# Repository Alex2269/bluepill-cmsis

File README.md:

```    
bluepill-cmsis:
examples SPL (Standard Peripheral Library).

StdPeriph_Lib=${HOME}/stm32lib/
mkdir  -p "${StdPeriph_Lib}"

sfm32f1 Libraries
unzip  zip-stm32f1_stdperiph_lib/stm32f1_stdperiph_lib.zip -d "${StdPeriph_Lib}"

rm stm32f1_stdperiph_lib.zip

depends: make cmake gcc g++ gcc-arm-none-eabi gdb-arm-none-eabi libusb-dev
apt install make cmake gcc g++ gcc-arm-none-eabi gdb-arm-none-eabi libusb-dev

port code from http://www.avislab.com/
```

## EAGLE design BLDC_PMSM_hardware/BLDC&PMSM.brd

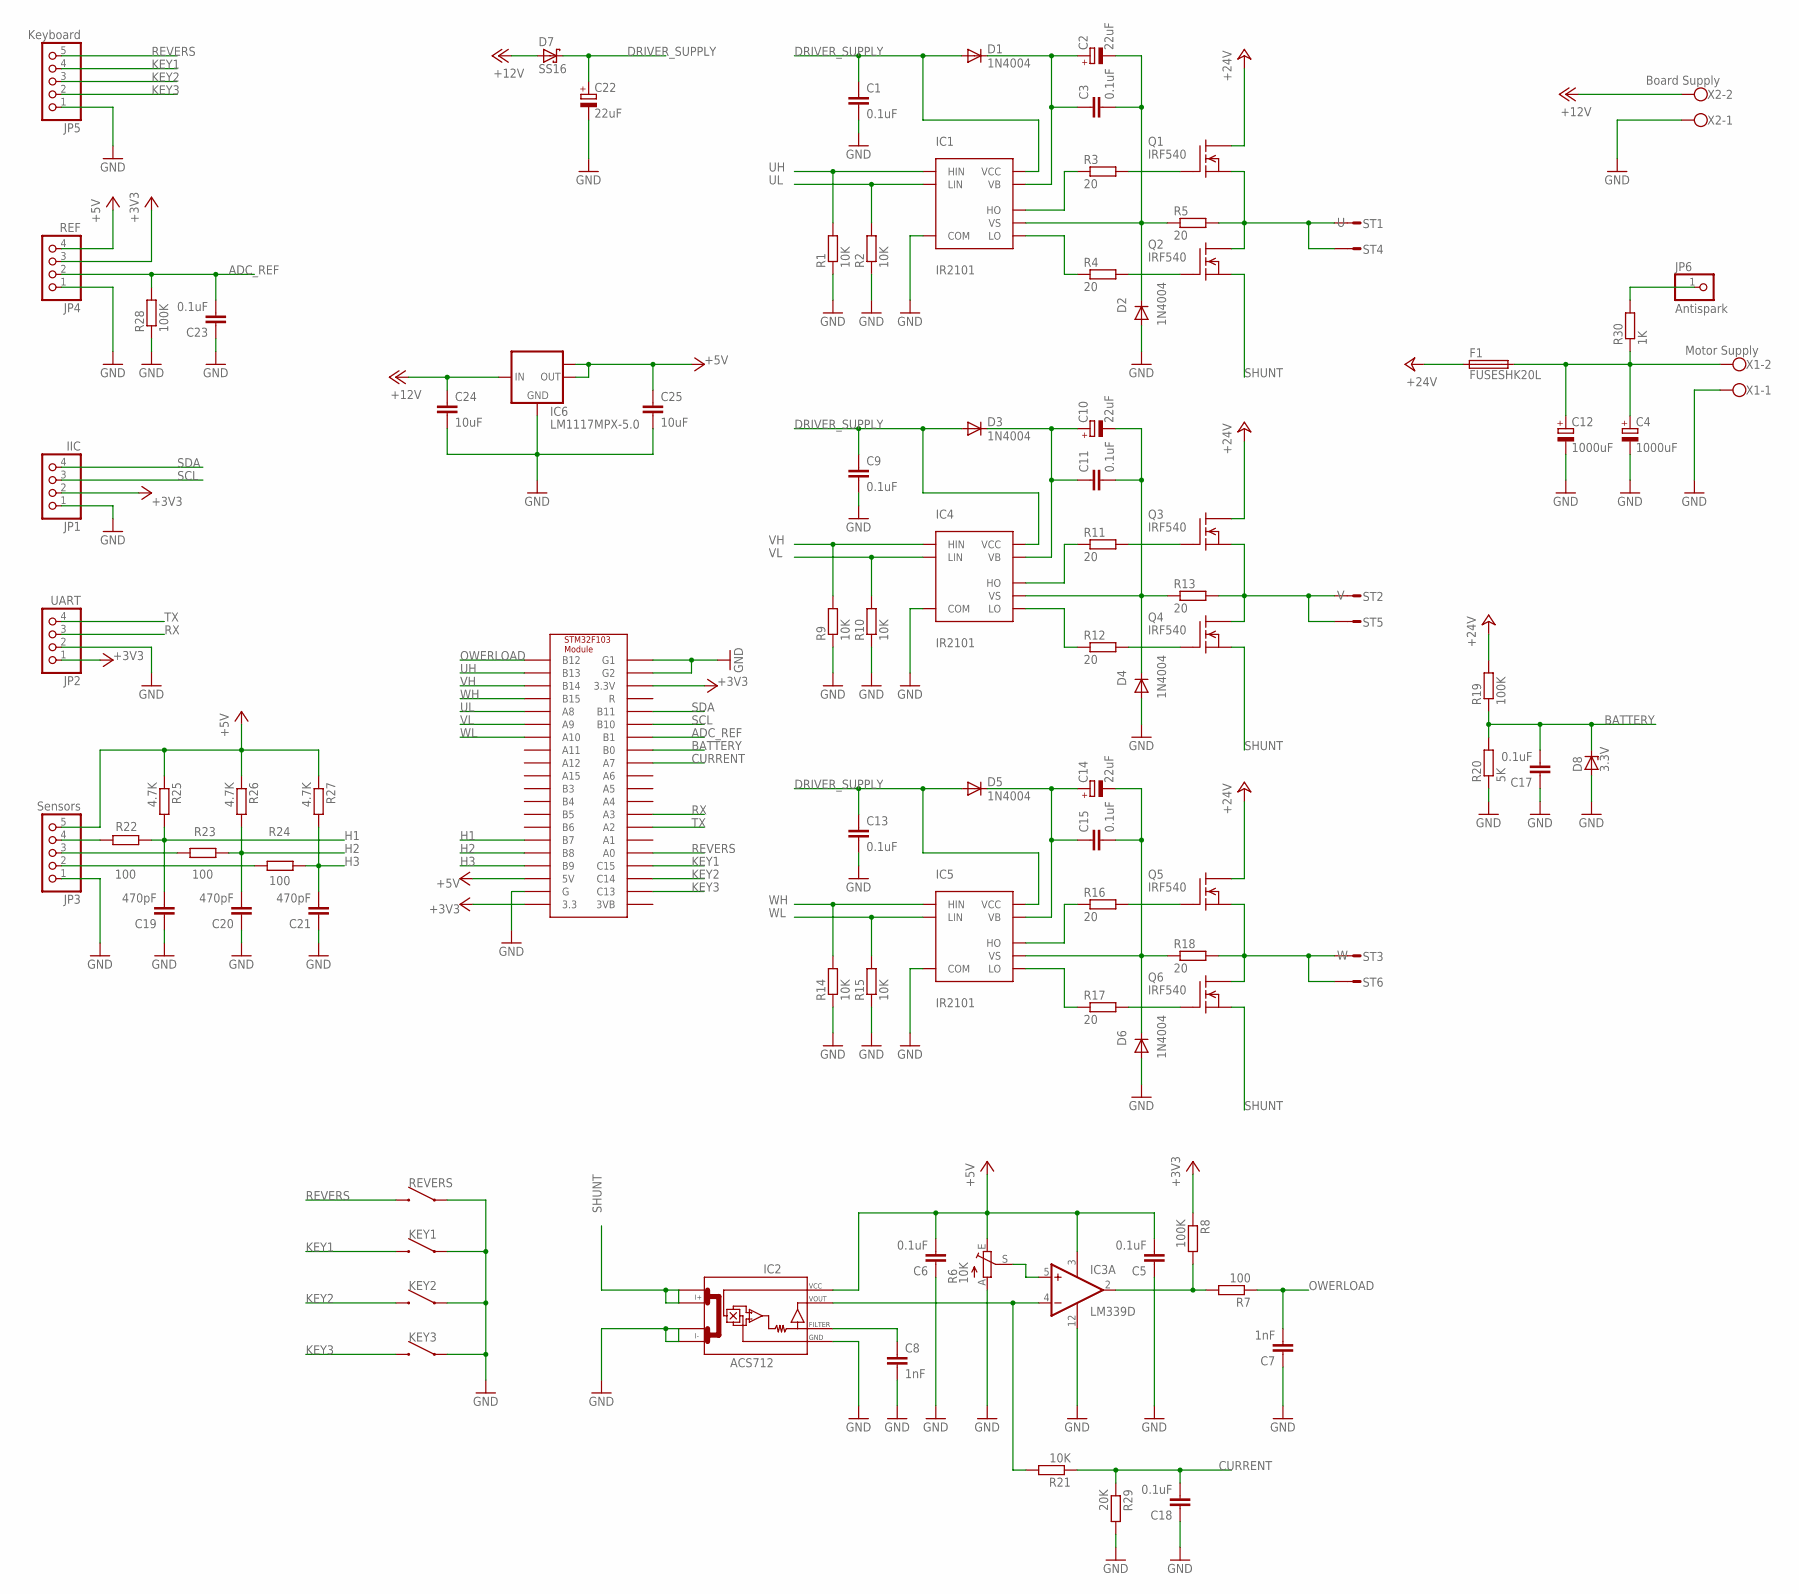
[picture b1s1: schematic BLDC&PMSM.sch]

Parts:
C1, C3, C5, C6, C9, C11, C13, C15, C17, C18, C23: 0.1uF; C0805K
C2, C10, C14, C22: 22uF; E2-5
C4, C12: 1000uF; E5-13
C7, C8: 1nF; C0805K
C19, C20, C21: 470pF; C0805K
C24: 10uF; C0805K
C25: 10uF; C1206K
D1, D2, D3, D4, D5, D6: 1N4004; DO41-10
D7: SS16; SMB
D8: 3.3V; SMB
F1: FUSESHK20L; SHK20L
IC1, IC4, IC5: IR2101; SO08
IC2: ACS712; SO08
IC3: LM339D; SO14
IC6: LM1117MPX-5.0; SOT223
JP1: IIC; 1X04
JP2: UART; 1X04
JP3: Sensors; 1X05
JP4: REF; 1X04
JP5: Keyboard; 1X05
JP6: Antispark; 1X01
KEY1, KEY2, KEY3: SWITCH
Q1, Q2, Q3, Q4, Q5, Q6: IRF540; TO220
R1, R2, R9, R10, R14, R15, R21: 10K; M0805
R3, R4, R5, R11, R12, R13, R16, R17, R18: 20; M0805
R6: 10K; CA6V
R7, R22, R23, R24: 100; M0805
R8, R19, R28: 100K; M0805
R20: 5K; M0805
R25, R26, R27: 4.7K; M0805
R29: 20K; M0805
R30: 1K; M0805
REVERS: SWITCH
ST1, ST2, ST3, ST4, ST5, ST6: ST2,8
U$1: STM32F103MODULE
X1: Motor Supply; W237-102
X2: Board Supply; W237-102

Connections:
3VB: U$1.P$40 (3VB)
+3V3: JP1.2, JP2.1, JP4.3, R8.1, U$1.P$20 (3.3), U$1.P$23 (3.3V)
+5V: C5.2, C6.2, C25.1, IC2.8 (VCC), IC3.3 (V+), IC6.2 (OUT), IC6.TAB (OUT1), JP3.5, JP4.4, R6.E, R25.1, R26.1, R27.1, U$1.P$18 (5V)
+12V: C24.1, D7.A, IC6.3 (IN), X2.2
+24V: F1.1A (1), Q1.2 (D), Q3.2 (D), Q5.2 (D), R19.2
ADC_REF: C23.2, JP4.2, R28.2, U$1.P$27 (B1)
BATTERY: C17.2, D8.C, R19.1, R20.2, U$1.P$28 (B0)
CURRENT: C18.2, R21.1, R29.1, U$1.P$29 (A7)
DRIVER_SUPPLY: C1.1, C9.1, C13.1, C22.+, D1.A, D3.A, D5.A, D7.C, IC1.1 (VCC), IC4.1 (VCC), IC5.1 (VCC)
GND: C1.2, C4.-, C5.1, C6.1, C7.1, C8.2, C9.2, C12.-, C13.2, C17.1, C18.1, C19.1, C20.1, C21.1, C22.-, C23.1, C24.2, C25.2, D2.A, D4.A, D6.A, D8.A, IC1.4 (COM), IC2.3 (I-_0), IC2.4 (I-_1), IC2.5 (GND), IC3.12 (GND), IC4.4 (COM), IC5.4 (COM), IC6.1 (GND), JP1.1, JP2.2, JP3.1, JP4.1, JP5.1, KEY1.P$2 (2), KEY2.P$2 (2), KEY3.P$2 (2), R1.1, R2.1, R6.A, R9.1, R10.1, R14.1, R15.1, R20.1, R28.1, R29.2, REVERS.P$2 (2), U$1.P$19 (G), U$1.P$21 (G1), U$1.P$22 (G2), X1.1, X2.1
H1: C19.2, R22.1, R25.2, U$1.P$15 (B7)
H2: C20.2, R23.1, R26.2, U$1.P$16 (B8)
H3: C21.2, R24.1, R27.2, U$1.P$17 (B9)
KEY1: JP5.4, KEY1.P$1 (1), U$1.P$37 (C15)
KEY2: JP5.3, KEY2.P$1 (1), U$1.P$38 (C14)
KEY3: JP5.2, KEY3.P$1 (1), U$1.P$39 (C13)
unnamed: IC3.5 (+IN), R6.S
unnamed: JP3.4, R22.2
unnamed: IC2.7 (VOUT), IC3.4 (-IN), R21.2
unnamed: IC3.2 (OUT), R7.2, R8.2
unnamed: Q1.1 (G), R3.2
unnamed: Q2.1 (G), R4.2
unnamed: IC1.7 (HO), R3.1
unnamed: IC1.5 (LO), R4.1
unnamed: C2.-, C3.2, D2.C, IC1.6 (VS), R5.1
unnamed: C2.+, C3.1, D1.C, IC1.8 (VB)
unnamed: C8.1, IC2.6 (FILTER)
unnamed: Q3.1 (G), R11.2
unnamed: Q4.1 (G), R12.2
unnamed: IC4.7 (HO), R11.1
unnamed: IC4.5 (LO), R12.1
unnamed: C10.-, C11.2, D4.C, IC4.6 (VS), R13.1
unnamed: C10.+, C11.1, D3.C, IC4.8 (VB)
unnamed: JP3.3, R23.2
unnamed: Q5.1 (G), R16.2
unnamed: Q6.1 (G), R17.2
unnamed: IC5.7 (HO), R16.1
unnamed: IC5.5 (LO), R17.1
unnamed: C14.-, C15.2, D6.C, IC5.6 (VS), R18.1
unnamed: C14.+, C15.1, D5.C, IC5.8 (VB)
unnamed: JP3.2, R24.2
unnamed: C4.+, C12.+, F1.2A (2), R30.1, X1.2
unnamed: JP6.1, R30.2
OWERLOAD: C7.2, R7.1, U$1.P$1 (B12)
REVERS: JP5.5, REVERS.P$1 (1), U$1.P$36 (A0)
RX: JP2.3, U$1.P$33 (A3)
SCL: JP1.3, U$1.P$26 (B10)
SDA: JP1.4, U$1.P$25 (B11)
SHUNT: IC2.1 (I+_0), IC2.2 (I+_1), Q2.3 (S), Q4.3 (S), Q6.3 (S)
TX: JP2.4, U$1.P$34 (A2)
U: Q1.3 (S), Q2.2 (D), R5.2, ST1.1, ST4.1
UH: IC1.2 (HIN), R1.2, U$1.P$2 (B13)
UL: IC1.3 (LIN), R2.2, U$1.P$5 (A8)
V: Q3.3 (S), Q4.2 (D), R13.2, ST2.1, ST5.1
VH: IC4.2 (HIN), R9.2, U$1.P$3 (B14)
VL: IC4.3 (LIN), R10.2, U$1.P$6 (A9)
W: Q5.3 (S), Q6.2 (D), R18.2, ST3.1, ST6.1
WH: IC5.2 (HIN), R14.2, U$1.P$4 (B15)
WL: IC5.3 (LIN), R15.2, U$1.P$7 (A10)

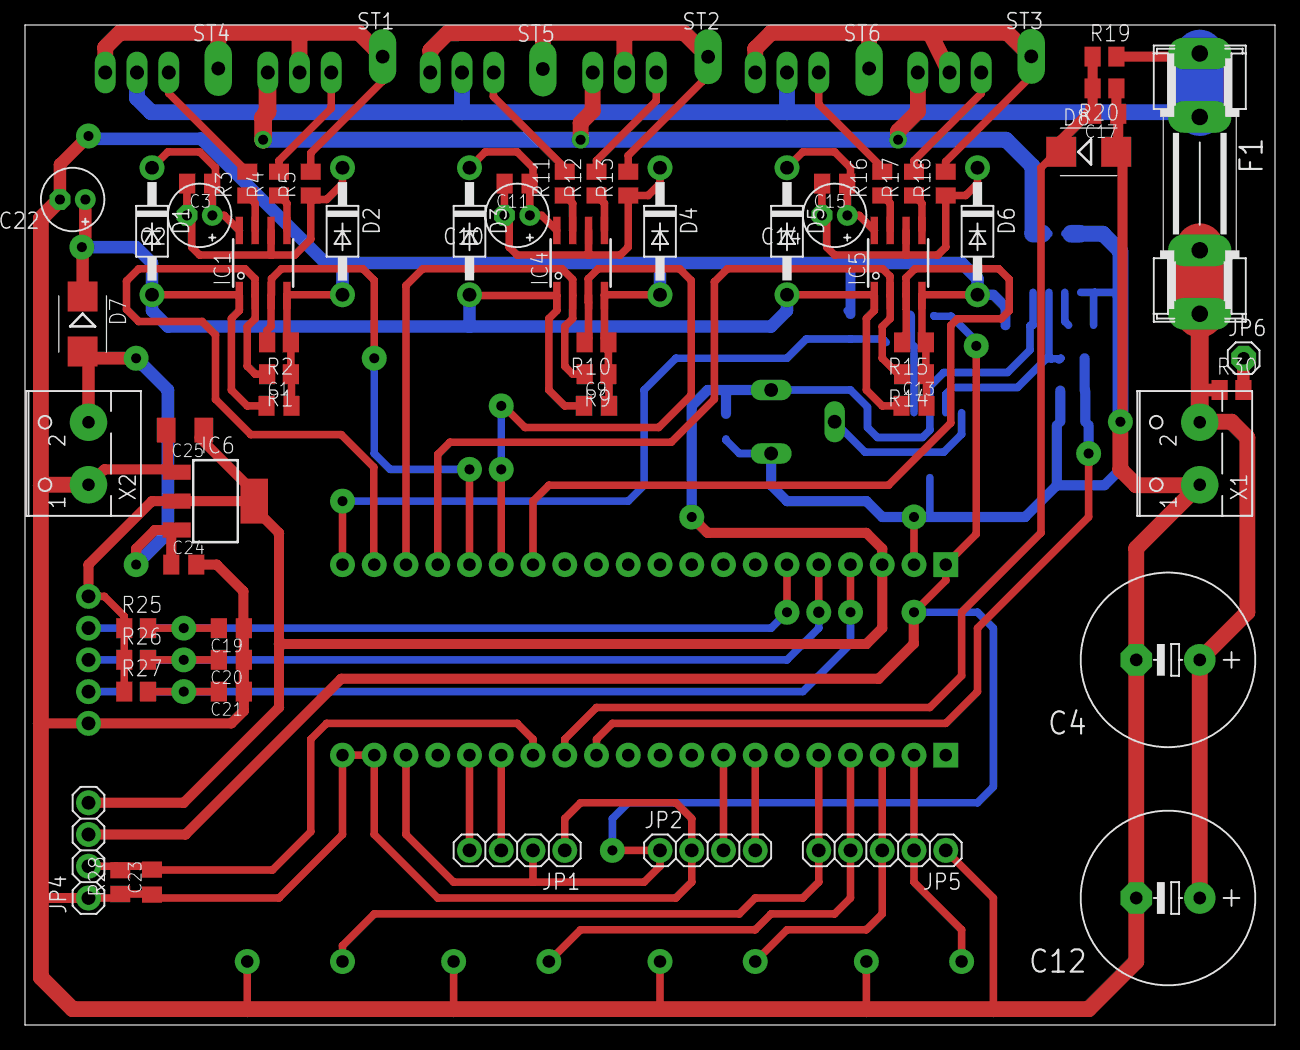
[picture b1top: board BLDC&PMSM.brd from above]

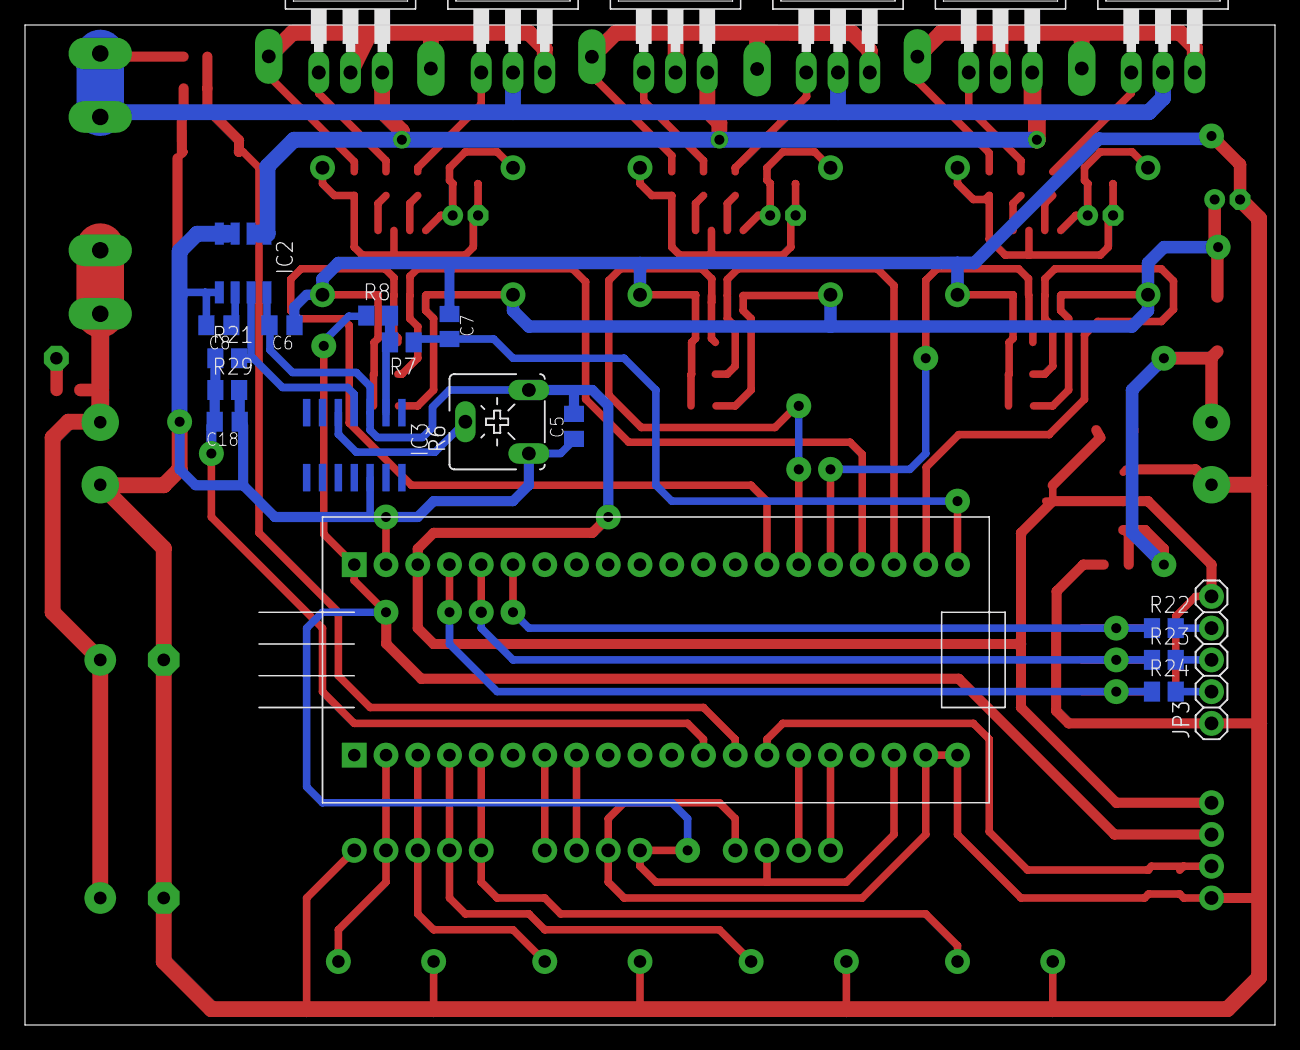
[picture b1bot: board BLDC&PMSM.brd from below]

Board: 2 copper layers, 100.0 x 80.0 mm, 94 parts (23 on the bottom side), 58 nets.

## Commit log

2019-11-09 2019-11-10
2019-11-24 2019-11-24
2019-12-02 2019-12-02
2021-02-21 2021-02-21
2021-02-21 2021-02-22
